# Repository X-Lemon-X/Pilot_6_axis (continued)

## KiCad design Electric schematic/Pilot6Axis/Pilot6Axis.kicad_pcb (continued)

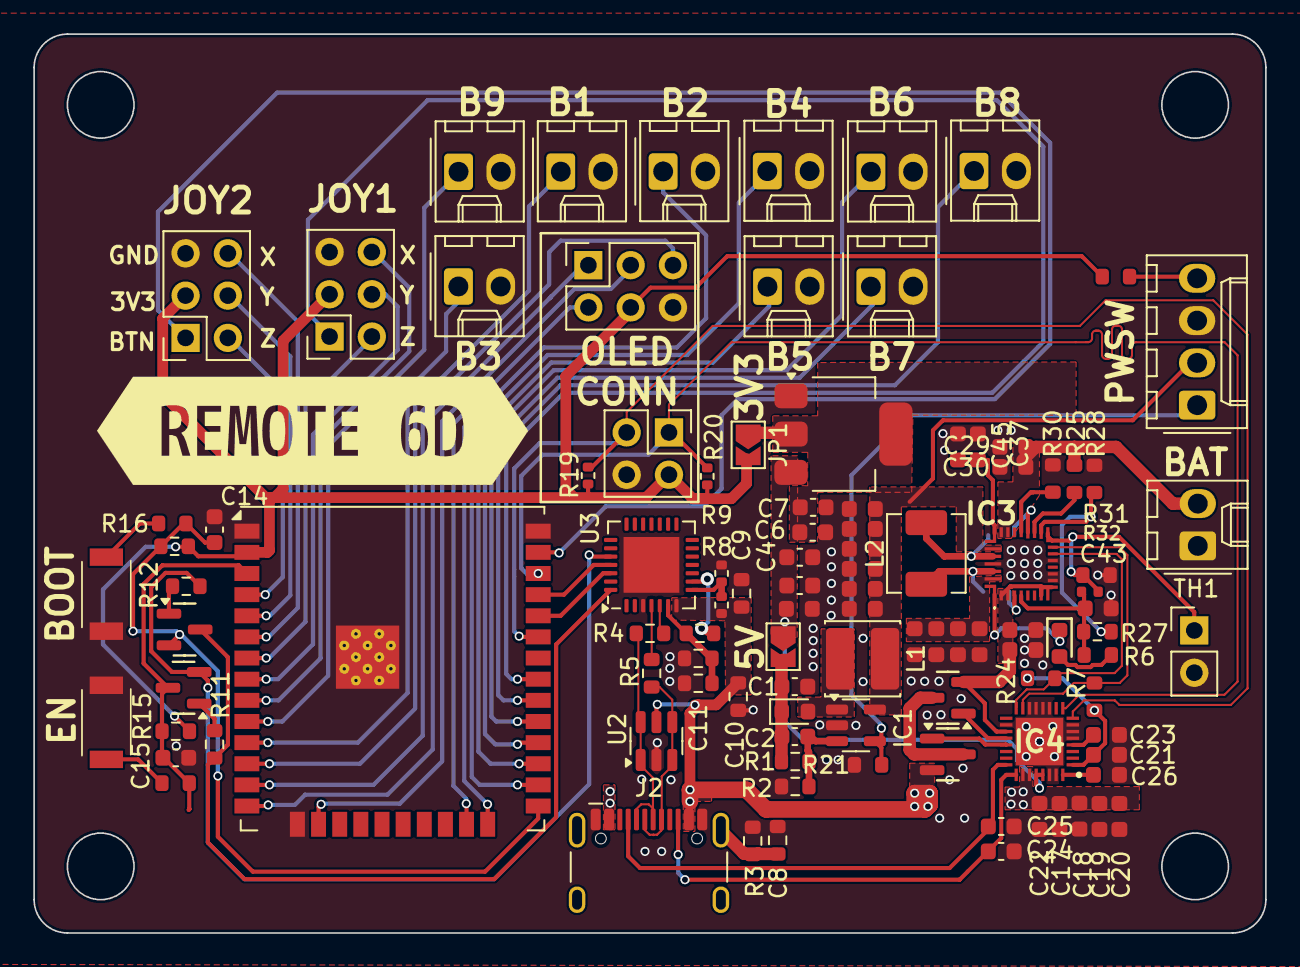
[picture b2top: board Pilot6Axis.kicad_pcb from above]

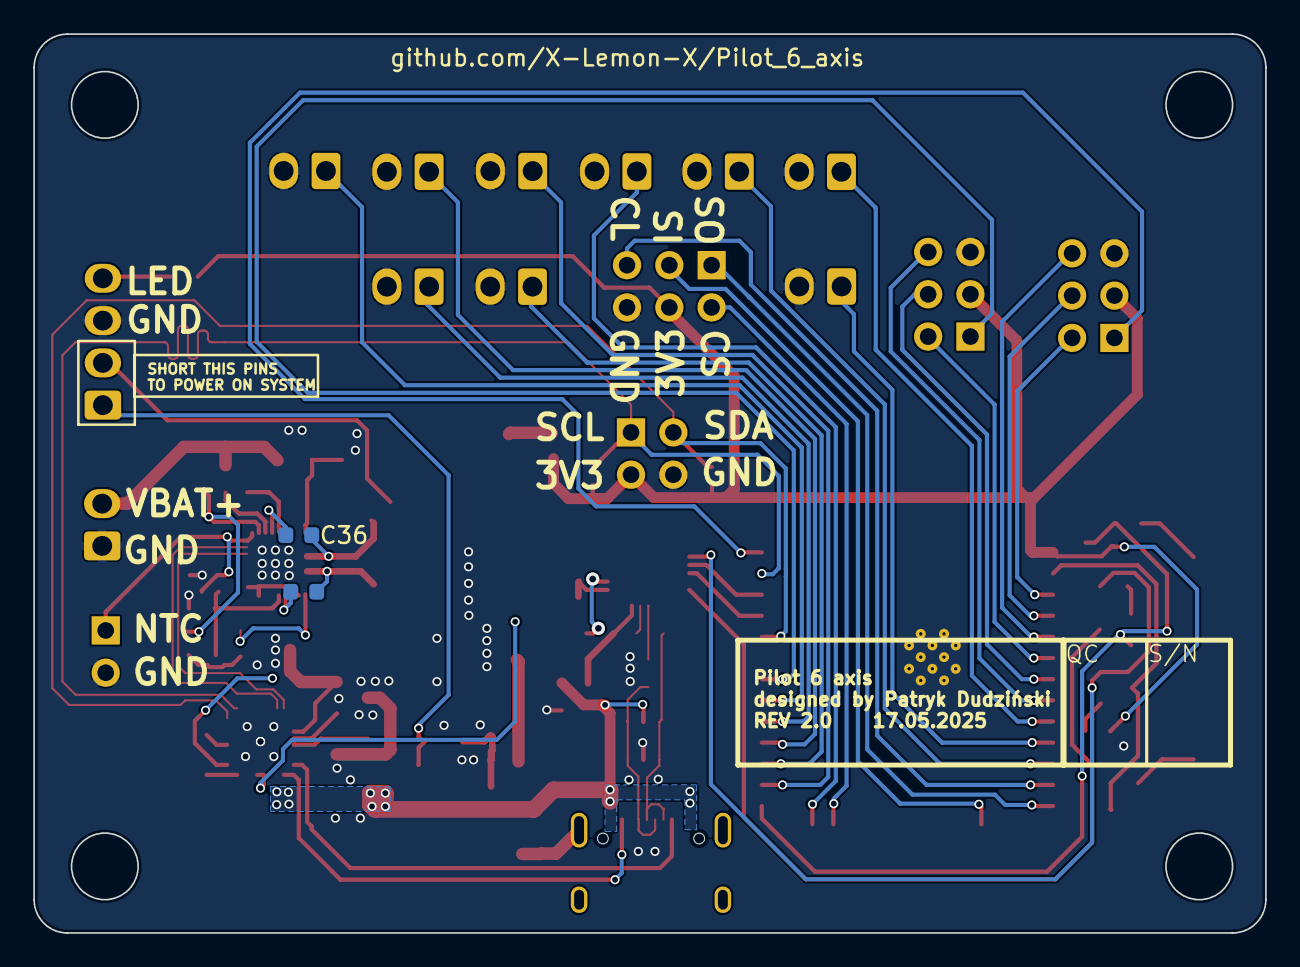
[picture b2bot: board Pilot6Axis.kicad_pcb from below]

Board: 2 copper layers, 74.0 x 54.0 mm, 107 parts (2 on the bottom side), 77 nets.

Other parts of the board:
kibuzzard-6828A41A: G***; kibuzzard-6828A41A

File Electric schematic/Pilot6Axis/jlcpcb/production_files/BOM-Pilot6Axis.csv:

Comment,Designator,Footprint,LCSC,Quantity
10uH,L1,L_Cenker_CKCS4018,C1035,1
470R,"R13,R14",R_0603_1608Metric,C114669,2
40.5k,R1,R_0603_1608Metric,C12447,1
100n,"C10,C11,C18,C19,C20,C26,C27,C28,C33,C4,C44,C7",R_0603_1608Metric,C14663,12
1k,R10,R_0603_1608Metric,C14676,1
1nF,"C13,C14,C15,C37,C45,C5,C6",C_0603_1608Metric,C1588,7
220pF,"C2,C24,C25",C_0603_1608Metric,C1603,3
47nF,"C35,C36",C_0603,C1622,2
4.7uF,"C1,C17,C43",C_0603_1608Metric,C19666,3
10u,"C12,C9",R_0603_1608Metric,C19702,2
S9014,"Q1,Q3",Q_SOT-23,C20069130,2
AO3400A,"Q2,Q4",Q_SOT-23,C20917,2
1kΩ,"R22,R6",R_0603,C21190,2
100Ω,R25,R_0603,C22775,1
Red,D4,D_0603,C2286,1
30kΩ,R31,R_0603,C22984,1
4.7kΩ,"R24,R7",R_0603,C23162,2
22Ω,"R17,R18",R_0603,C23345,2
2.2uF,C3,C_0603_1608Metric,C23630,1
100kΩ,R28,R_0603,C25803,1
10kΩ,R21,R_0603,C25804,1
5.1kΩ,R32,R_0402,C25905,1
13.3k,"R11,R12,R15,R16,R19,R2,R20,R8,R9",R_0603_1608Metric,C25952,9
USB_C_Receptacle_USB2.0_16P,J2,USB_C_Receptacle_HCTL_HC-TYPE-C-16P-01A,C2765186,1
MBR0520,D1,D_0603_1608Metric,C2858712,1
LM27313XMFX_NOPB,IC1,SOT-23-5,C341750,1
3kΩ,R30,R_0603,C4211,1
33k,R3,R_0603_1608Metric,C4216,1
SW_Push,"SW1,SW2",TS1088R02026,C455280,2
USBLC6-2SC6,U2,SOT-23-6,C5180249,1
10nF,C8,R_0603_1608Metric,C57112,1
AMS1117-3.3,U1,SOT-223-3_TabPin2,C6186,1
22R,"R4,R5",R_0603_1608Metric,C71618,2
10uF,"C16,C21,C22,C23,C29,C30,C31,C32,C34,C38,C39,C40,C41,C42",C_0603,C96446,14
CP2102N-Axx-xQFN28,U3,QFN-28-1EP_5x5mm_P0.5mm_EP3.35x3.35mm,C964632,1
BTN7,J12,Molex_KK-254_AE-6410-02A_1x02_P2.54mm_Vertical,,1
Conn_02x03_Odd_Even,J3,PinSocket_2x03_P2.54mm_Vertical,,1
BTN3,J8,Molex_KK-254_AE-6410-02A_1x02_P2.54mm_Vertical,,1
BTN4,J9,Molex_KK-254_AE-6410-02A_1x02_P2.54mm_Vertical,,1
BTN9,J14,Molex_KK-254_AE-6410-02A_1x02_P2.54mm_Vertical,,1
BTN8,J13,Molex_KK-254_AE-6410-02A_1x02_P2.54mm_Vertical,,1
Battery input,J1,Molex_KK-254_AE-6410-02A_1x02_P2.54mm_Vertical,,1
BTN5,J10,Molex_KK-254_AE-6410-02A_1x02_P2.54mm_Vertical,,1
Oled,J5,PinSocket_2x02_P2.54mm_Vertical,,1
BTN2,J7,Molex_KK-254_AE-6410-02A_1x02_P2.54mm_Vertical,,1
BTN6,J11,Molex_KK-254_AE-6410-02A_1x02_P2.54mm_Vertical,,1
Oled,J16,PinSocket_2x03_P2.54mm_Vertical,,1
Power switch,J15,Molex_KK-254_AE-6410-04A_1x04_P2.54mm_Vertical,,1
BTN1,J6,Molex_KK-254_AE-6410-02A_1x02_P2.54mm_Vertical,,1
ESP32-WROOM-32U,U4,ESP32-WROOM-32U,,1
Conn_02x03_Odd_Even,J19,PinSocket_2x03_P2.54mm_Vertical,,1
127k,R27,R_0603_1608Metric,,1
TPS25751SRSMR,IC4,QFN40P400X400X100-33N-D,,1
SolderJumper_2_Bridged,JP1,SolderJumper-2_P1.3mm_Open_TrianglePad1.0x1.5mm,,1
SolderJumper_2_Bridged,JP300,SolderJumper-2_P1.3mm_Open_TrianglePad1.0x1.5mm,,1
10k,TH1,PinHeader_1x02_P2.54mm_Vertical,,1
BQ25792RQMR,IC3,BQ25792RQMR,,1
1u,L2,L_APV_APH0420,,1

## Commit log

2022-10-31 Inicjalizacja
2022-11-01 naprawa błędu oledmeny
2022-11-02 wprowadzony nowe funkcje kalsy OLEDMENU lista pobieranie itemów tworzenie folderów i tworzenie elementów nie testowane dadana struktowa union na dane
2022-11-03 nowa wersja oledMenu wyszukiwanie item ow z tej samej grup ddoane
2022-11-18 dodany check wifi
2022-11-27 zmiana usunicie czasu z czytania analogowego
2022-12-29 small fixes to Jyostick class adding web server with acces point early stage
2022-12-30 pahe setup added
2022-12-30 aded new ewb design adn setings funcions
2022-12-30 testy strony
2022-12-30 upate setings with mian
2022-12-31 added setings adder to string converter
2023-01-01 added wifi all config saving in EEPROM wifi menaging setup websiet auto ceonnection to availabel networks
2023-01-01 added wifi all config saving in EEPROM wifi menaging setup websiet auto ceonnection to availabel networks samll loop error fixed
2023-01-01 poprawka
2023-02-11 init pilota V2 klasa z wyżwietlaniem lini na oledzie styl linux przeniesiona dożo błedów XD
2023-02-13 port change
2023-02-13 smal tets fir errors
2023-02-13 dobre zmianuy
2023-02-14 update pronlmry rozwizane z klasa OledPrintLib
2023-02-14 update pronlmry rozwizane z klasa OledPrintLib dodanei pliku cpp
2023-02-16 problem with esp restart detetected SF upgraded partialy to vector
2023-02-20 olmost entirely working xd
2023-02-20 added python script to interpretate date acomig from a Remote and cpp files no code empty
2023-02-22 test czasu pracy pilota
2023-12-29 fixed issues, moved all to freeRtos wifi send is working, added python reciver
2023-12-29 optimized oled dislay added debug info
2023-12-29 added readme
2023-12-30 changed website color, updated readme
2023-12-30 added descritpion list aprt iamges, updated readme
2023-12-30 fixed image issue
2023-12-30 added schematics
2023-12-31 added few stuff to readme
2023-12-31 made small changes ti folder system
2024-01-12 fixed missing t from settings verrb
2024-01-19 added Ros stuff
2024-01-20 now working
2024-01-23 Create LICENSE
2024-01-23 Update LICENSE
2024-02-07 added someting
2024-02-07 to do
2024-02-07 fixed ros and added filtering and stuff
2024-02-11 added stl files
2024-02-11 added new 3mf files
2024-02-13 added keyboard pilot fixed some issues in pilot
2024-02-22 changed button 8 to space for dead man switch
2024-04-20 chnaged timeout on wifi conenction
2024-05-13 update git ignore
2024-06-10 added new publisher for gripper
2024-06-17 fixed issue with wifi conencting 2 times insteda of one, code optimized, added acces point config
2024-06-23 added new styles for a pilot
2024-09-22 added init so it can be easily impoerted as ros2 moduel
2024-09-22 added gitignore
2024-09-25 added params
2024-10-01 updaet ros
2025-02-09 added pcb files
2025-02-21 added rev number and projekct info
2025-02-21 backup
2025-02-21 update reciver chnaged topics
2025-02-26 [ros] added rc recived as ros package with rc node , update readme with instructions
2025-02-26 clean up code
2025-03-05 fixed requiremtnts file
2025-03-05 removed requiremtns py
2025-03-08 added step files
2025-04-24 update to use new naming of th emoduel
2025-05-05 added licence and author
2025-05-15 update schematic to kicajd 9.0, fixed usb D=/D- wrongly inerconnected , otherwise pcb seems to be woekring
2025-05-16 [firmware] upgrade firmware do be l;ess diabolic,, fixed problew witf slow conenction of witfi, upgrade websie UI
2025-05-16 added boom file
2025-05-17 upgrade board to use USB BD for power delivery and addded SPI screen conector
2025-05-19 [screen] addd status bar
2025-05-20 [pcb] cleanup schematics, made power trace slightl less intterfiring with usb
2025-05-22 [pd] added 5V to PD
2025-05-22 fixed leyout
2025-05-22 added gerber files
2025-05-23 update requiremenst
2025-06-14 update gerber
2025-07-19 [Pilot V2] PCB Rev 3.0| PD, WIFI| extendable IO| embeded switches, new conenctors, extenstion conenctors, new ON/OFF circuit
2025-07-19 Removed unnecesary files
2025-07-21 update step
2025-07-24 [pcb] added eeprom to pd charger so the ciofnig is remembered and set correctly
